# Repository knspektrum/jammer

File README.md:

# jammer

Milestones:
2026-04 - Finish research and ensure that everyone understands it.
2026-05 - Simulate core components. Complete simulation of both hardware and software (modulation/demodulation).
2026-06 - Order parts for the prototype like FPGA devboards.
2026-07 - Complete the prototype and develop software to jam things supported by the NRF jammer, implement signal reception and decoding.
2026-08 - Design the final PCB and place the order.

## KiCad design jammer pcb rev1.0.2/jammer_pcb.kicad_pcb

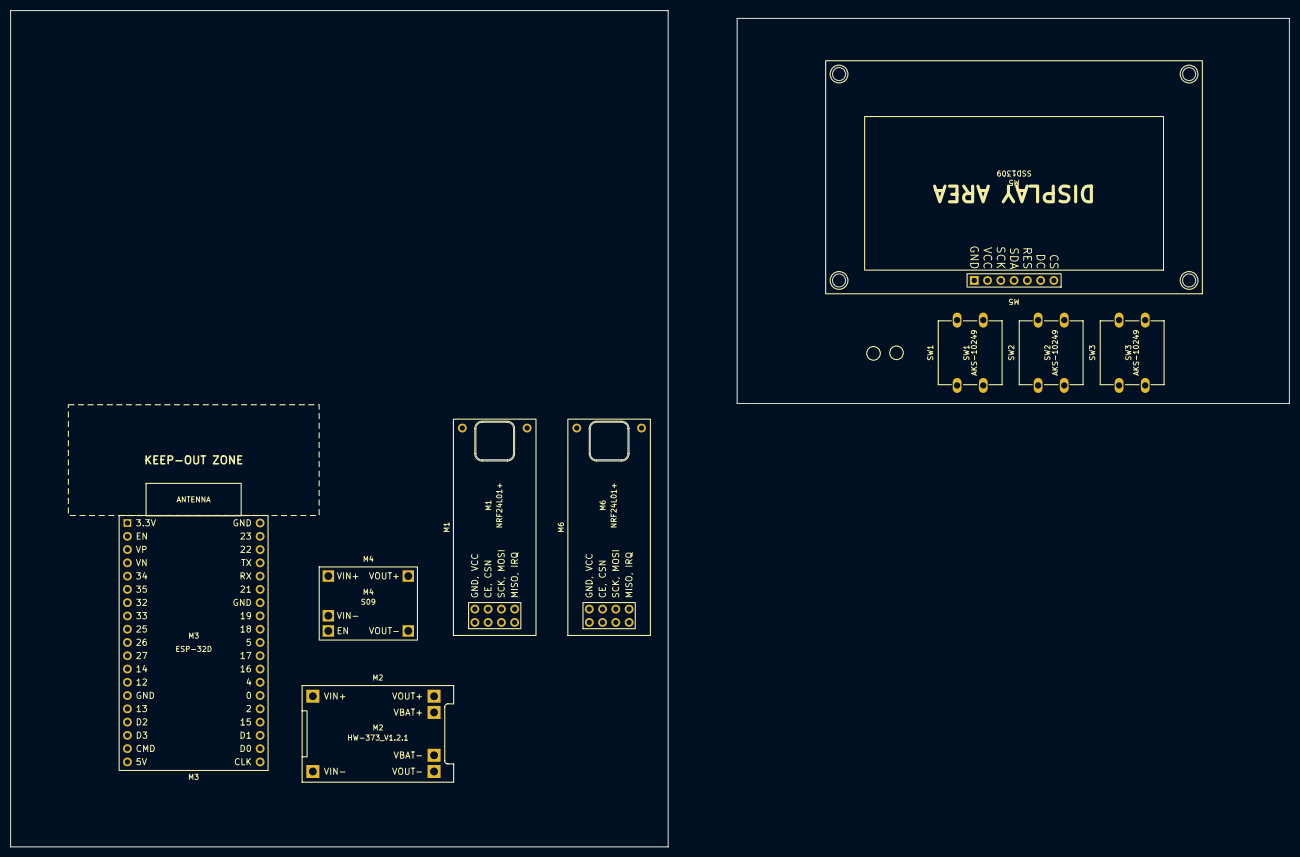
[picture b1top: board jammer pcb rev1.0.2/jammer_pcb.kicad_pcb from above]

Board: 2 copper layers, 244.8 x 160.1 mm, 9 parts (0 on the bottom side), 3 nets, no tracks yet.

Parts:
M1, M6: NRF24L01+; Radio Module
M2: HW-373_V1.2.1; Battery Charger Layout
M3: ESP-32D; ESP32
M4: S09; Converter
M5: SSD1309; 2.42'' OLED Display Layout
SW1, SW2, SW3: AKS-10249; Button

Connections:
unnamed: SW1.1 (A), SW1.2 (A)
unnamed: SW2.1 (A), SW2.2 (A)
unnamed: SW3.1 (A), SW3.2 (A)

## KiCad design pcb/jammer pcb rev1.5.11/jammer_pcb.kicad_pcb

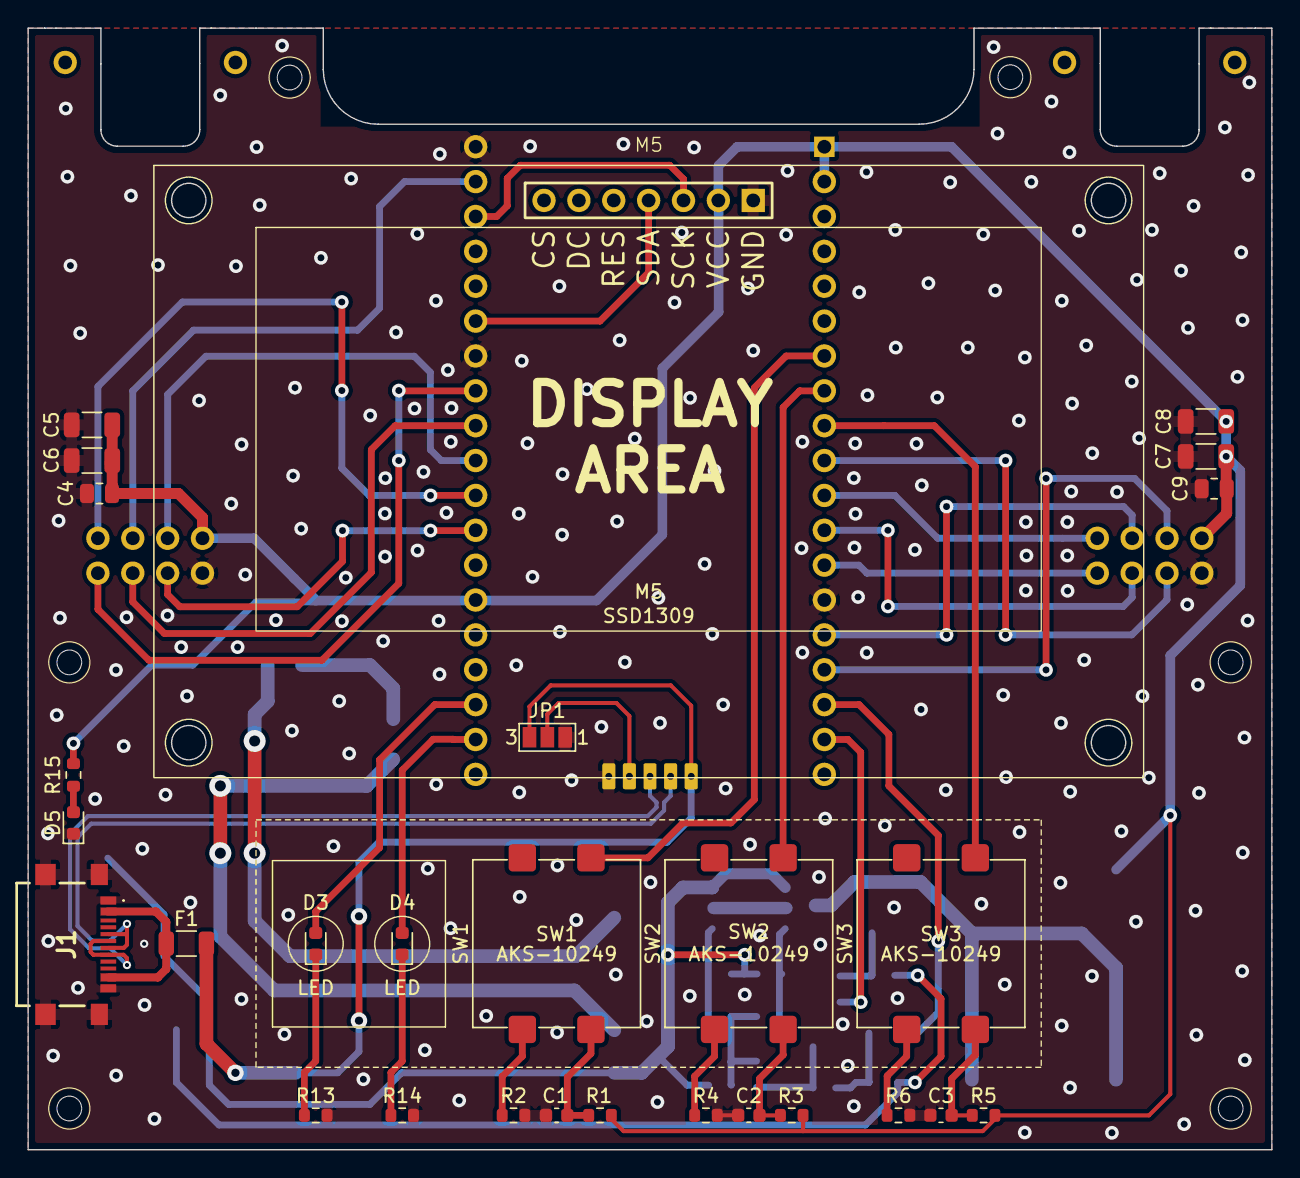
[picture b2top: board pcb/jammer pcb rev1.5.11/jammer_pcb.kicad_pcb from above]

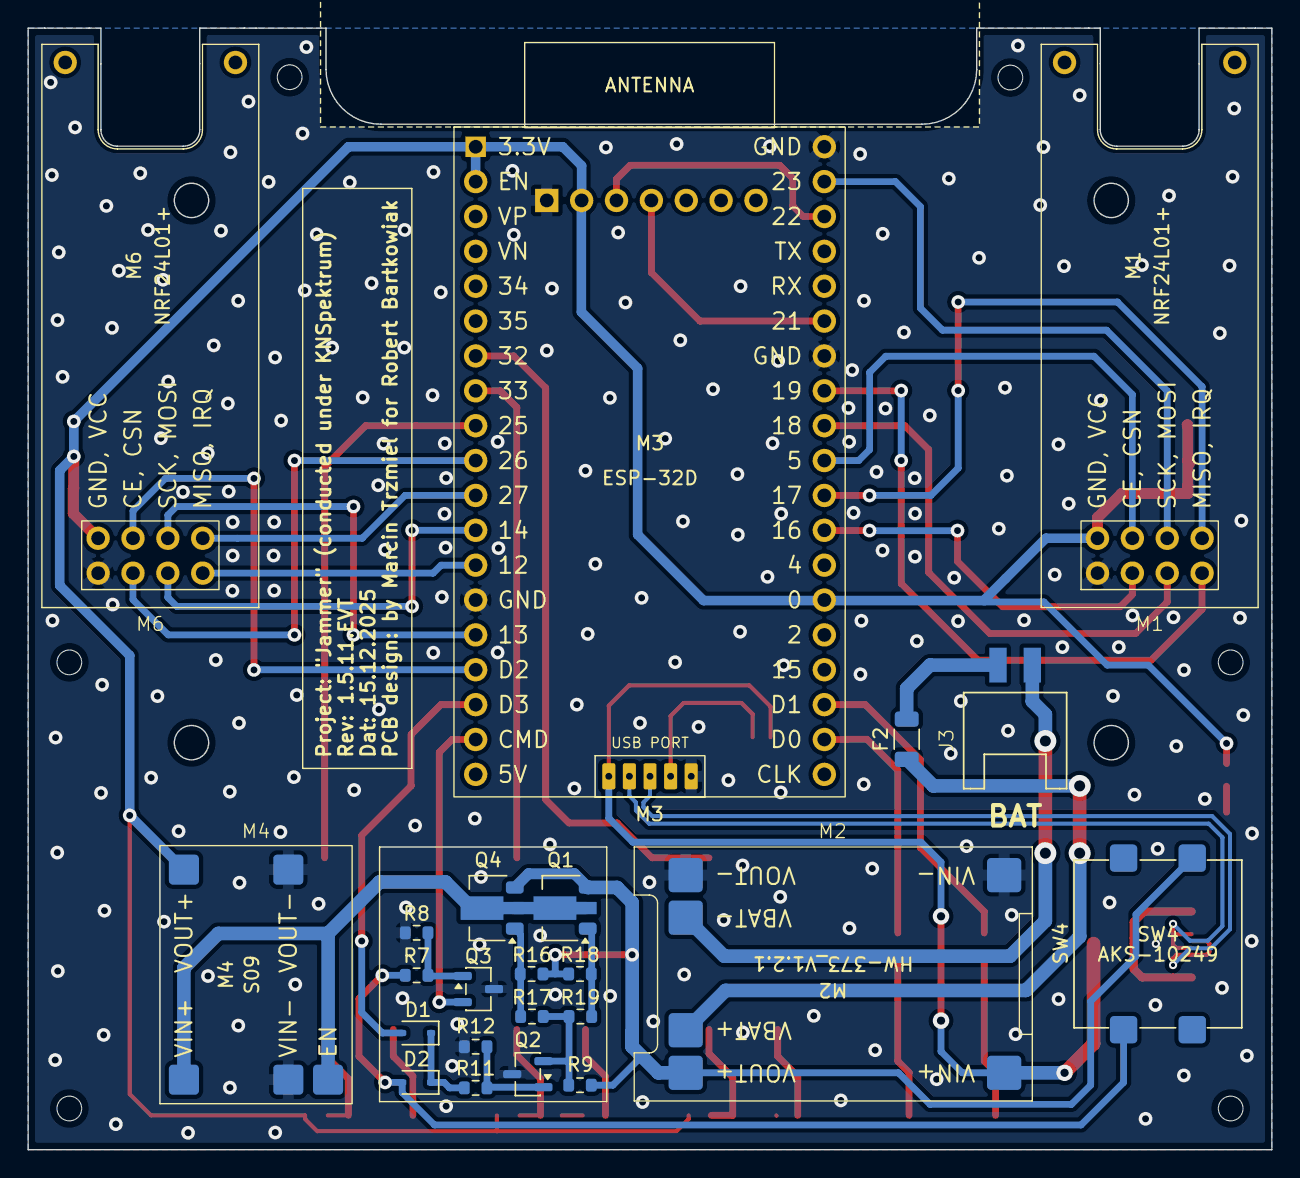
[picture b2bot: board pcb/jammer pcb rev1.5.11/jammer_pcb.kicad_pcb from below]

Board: 2 copper layers, 90.6 x 81.7 mm, 51 parts (23 on the bottom side), 46 nets.

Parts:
C1, C2, C3: 100nF; C_0603_1608Metric
C4, C9: 100nF; R_0805_2012Metric
C5, C6, C7, C8: 10uF; C_1206_3216Metric
D1, D2: D; D_SOD-323
D3, D4, D5: LED; D_0603_1608Metric
F1, F2: Fuse; R_1206_3216Metric
J1: USB4216-03-A; USB Port
J3: Bat_Conn; 2pin Socket
JP1: Jumper_3_Open; SolderJumper-3_P1.3mm_Open_Pad1.0x1.5mm_NumberLabels
M1, M6: NRF24L01+; Radio Module
M2: HW-373_V1.2.1; Battery Charger Layout
M3: ESP-32D; ESP32
M4: S09; Converter
M5: SSD1309; 2.42'' OLED Display Layout
Q1, Q4: PNP; SOT-89-3
Q2, Q3: NPN; SOT-23-3
R1, R3, R5: 10kR; R_0603_1608Metric
R2, R4, R6: 330R; R_0603_1608Metric
R7, R8, R9, R11, R12, R16, R17, R18, R19: R; R_0603_1608Metric
R13, R14, R15: 500R; R_0603_1608Metric
SW1, SW2, SW3, SW4: AKS-10249; Button

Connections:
3.3V: C4.1, C5.1, C6.1, C7.1, C8.1, C9.1, M1.2 (VCC), M3.1 (3.3V), M3.2 (EN), M3.33 (0), M4.4 (VOUT+), M5.2 (VCC), M6.2 (VCC), R1.1, R3.1, R5.1, R15.1
D+: J1.A6 (DP1), J1.B6 (DP2), M3.41 (D+)
D-: J1.A7 (DN1), J1.B7 (DN2), M3.40 (D-)
GND: C1.2, C2.2, C3.2, C4.2, C5.2, C6.2, C7.2, C8.2, C9.2, D5.1 (K), J1.A1 (GND_1), J1.B1 (GND_2), J1.G1 (GND_3), J1.G2 (GND_4), J1.G3 (GND_5), J1.G4 (GND_6), JP1.1 (A), M1.1 (GND), M2.2 (VIN-), M2.6 (VOUT-), M3.14 (GND), M3.20 (GND), M3.26 (GND), M3.43 (GND), M4.2 (VIN-), M4.5 (VOUT-), M5.1 (GND), M6.1 (GND), Q2.3 (E), Q3.3 (E), R2.2, R4.2, R6.2, R8.2, R12.2, R13.2, R14.2
HCE: M3.10 (26), M6.3 (CE)
HCLK: M3.12 (14), M6.5 (SCK)
HCS: M3.16 (D2), M6.4 (CSN)
HIRQ: M3.11 (27), M6.8 (IRQ)
HMISO: M3.13 (12), M6.7 (MISO)
HMOSI: M3.15 (13), M6.6 (MOSI)
LED1: D3.2 (A), M3.36 (D1)
LED2: D4.2 (A), M3.37 (D0)
MAIN: M4.1 (VIN+), M4.3 (EN), Q1.2 (C), Q4.2 (C)
unnamed: D1.1 (K), D2.1 (K), R11.1
unnamed: D2.2 (A), R7.1, SW4.2 (B)
unnamed: D3.1 (K), R13.1
unnamed: D4.1 (K), R14.1
unnamed: D5.2 (A), R15.2
unnamed: F1.2, J1.A4 (VBUS_1), J1.B4 (VBUS_2)
unnamed: F2.2, J3.1
unnamed: J3.2, M2.5 (VBAT-)
unnamed: JP1.2 (C), M3.42 (ID)
unnamed: F2.1, M2.4 (VBAT+)
unnamed: Q1.1 (B), R18.2, R19.1
unnamed: Q2.1 (B), R11.2, R12.1
unnamed: Q2.2 (C), R9.2, R17.2, R19.2
unnamed: Q3.1 (B), R7.2, R8.1
unnamed: Q4.1 (B), R16.2, R17.1
unnamed: R2.1, SW1.1 (A)
unnamed: R4.1, SW2.1 (A)
unnamed: R6.1, SW3.1 (A)
PBS: D1.2 (A), M3.17 (D3)
PSS: M3.18 (CMD), Q3.2 (C)
SCL: M3.22, M5.3 (SCK)
SDA: M3.25 (21), M5.4 (SDA)
SW1: C1.1, M3.7 (32), R1.2, SW1.2 (B)
SW2: C2.1, M3.8 (33), R3.2, SW2.2 (B)
SW3: C3.1, M3.9 (25), R5.2, SW3.2 (B)
USB: F1.1, JP1.3 (B), M2.1 (VIN+), M3.39 (VCC)
VCC: M2.3 (VOUT+), Q1.3 (E), Q4.3 (E), R9.1, R16.1, R18.1, SW4.1 (A)
VCE: M1.3 (CE), M3.31 (16)
VCLK: M1.5 (SCK), M3.28 (18)
VCS: M1.4 (CSN), M3.29 (5)
VIRQ: M1.8 (IRQ), M3.30 (17)
VMISO: M1.7 (MISO), M3.27 (19)
VMOSI: M1.6 (MOSI), M3.21 (23)

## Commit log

2026-04-17 add research docs
2026-04-20 Wymagane części.md
2026-04-20 Potrzebne części i schematy.md
2026-04-23 milestones
